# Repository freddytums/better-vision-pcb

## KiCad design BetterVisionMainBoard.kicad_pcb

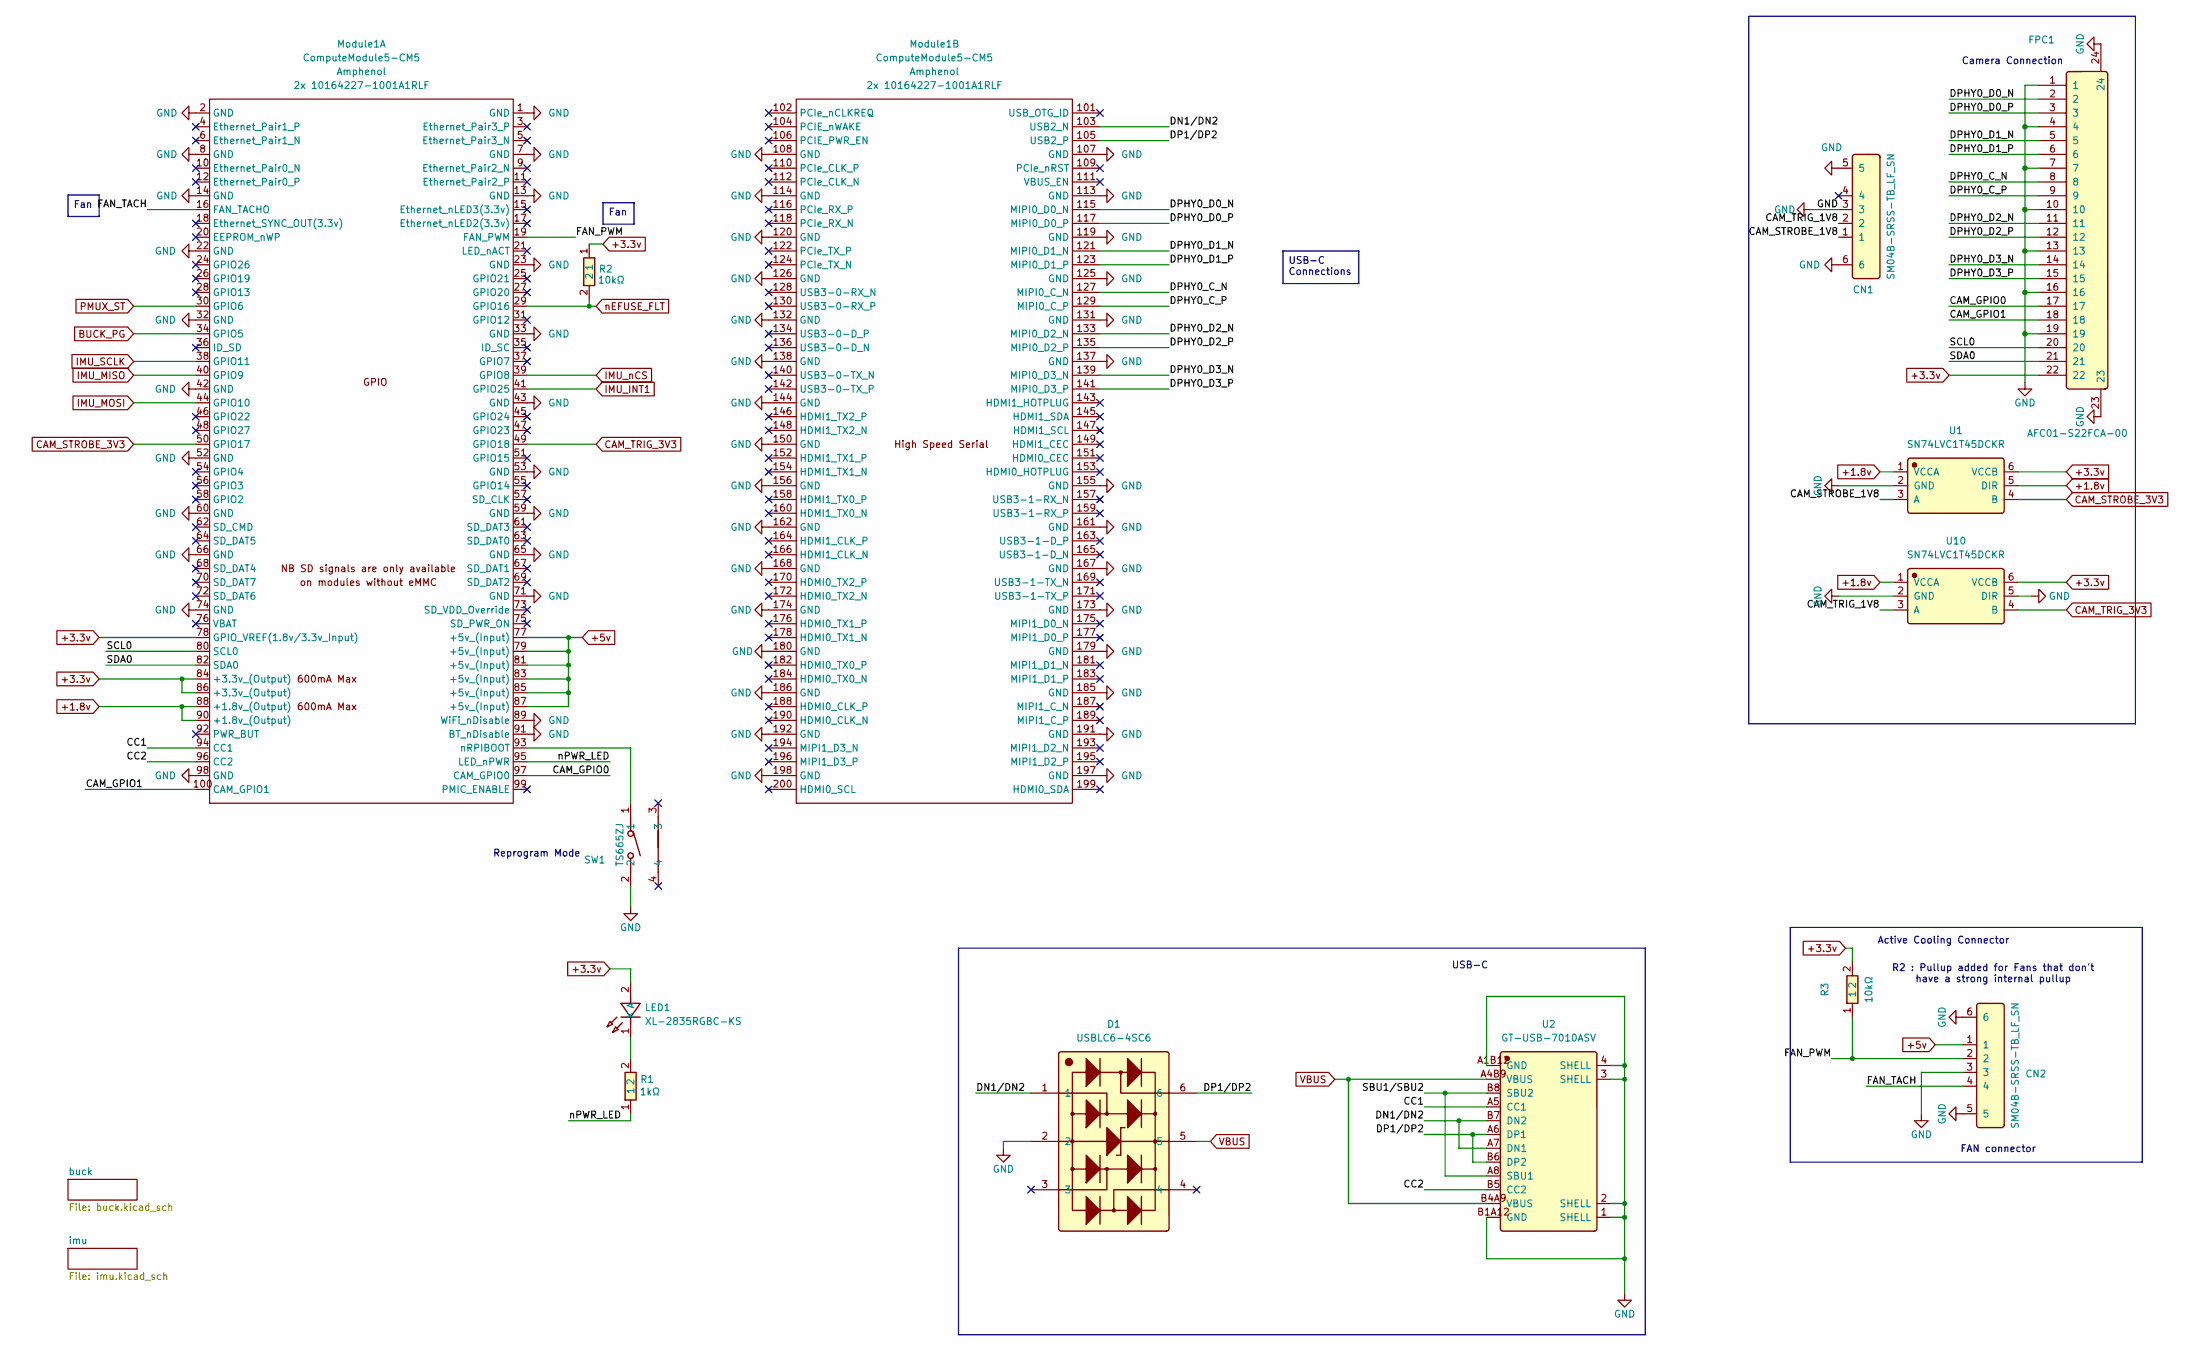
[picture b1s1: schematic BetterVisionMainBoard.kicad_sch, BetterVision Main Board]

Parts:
CN1, CN2: SM04B-SRSS-TB_LF_SN; Manufacturer Part SM04B-SRSS-TB(LF)(SN); LCSC C160404
D1: USBLC6-4SC6; MPN USBLC6-4SC6; LCSC Part C111212
FPC1: AFC01-S22FCA-00; Part Description 22 Position FFC, FPC Connector Contacts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; LCSC Part C262668
LED1: XL-2835RGBC-KS; MPN XL-2835RGBC-KS; LCSC Part C2843781
Module1: ComputeModule5-CM5; Raspberry-Pi-5-Compute-Module; MPN 10164227-1001A1RLF; LCSC Part C6782225
R1: 1kΩ; RC0402FR-071KL; Part Description Resistor 1K M1005 1% 63mW; LCSC Part C106235
R2: 10kΩ; RC0402FR-0710KL; MPN RC0402FR-0710KL; LCSC Part C60490
R3: 10kΩ; RC0402FR-0710KL; Part Description Resistor 10K M1005 1% 63mW; LCSC Part C60490
SW1: TS665ZJ; Part Description Right angle through hole Tact switch; LCSC Part C557599
U1, U10: SN74LVC1T45DCKR; MPN SN74LVC1T45DCKR; LCSC Part C9382
U2: GT-USB-7010ASV; MPN GT-USB-7010ASV; LCSC Part C2988369

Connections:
+1.8v: Module1.88 (+1.8v_(Output)), Module1.90 (+1.8v_(Output)), U1.1 (VCCA), U1.5 (DIR), U10.1 (VCCA)
+3.3v: FPC1.22, LED1.2 (A), Module1.78 (GPIO_VREF(1.8v/3.3v_Input)), Module1.84 (+3.3v_(Output)), Module1.86 (+3.3v_(Output)), R2.1, R3.2, U1.6 (VCCB), U10.6 (VCCB); also elsewhere on the board
+5v: CN2.1, Module1.77 (+5v_(Input)), Module1.79 (+5v_(Input)), Module1.81 (+5v_(Input)), Module1.83 (+5v_(Input)), Module1.85 (+5v_(Input)), Module1.87 (+5v_(Input)); also elsewhere on the board
/CAM_GPIO0: FPC1.17, Module1.97 (CAM_GPIO0)
/CAM_GPIO1: FPC1.18, Module1.100 (CAM_GPIO1)
/CAM_STROBE_1V8: CN1.1, U1.3 (A)
/CAM_TRIG_1V8: CN1.2, U10.3 (A)
/CC1: Module1.94 (CC1), U2.A5 (CC1)
/CC2: Module1.96 (CC2), U2.B5 (CC2)
/DN1/DN2: D1.1, Module1.103 (USB2_N), U2.A7 (DN1), U2.B7 (DN2)
/DP1/DP2: D1.6, Module1.105 (USB2_P), U2.A6 (DP1), U2.B6 (DP2)
/DPHY0_C_N: FPC1.8, Module1.127 (MIPI0_C_N)
/DPHY0_C_P: FPC1.9, Module1.129 (MIPI0_C_P)
/DPHY0_D0_N: FPC1.2, Module1.115 (MIPI0_D0_N)
/DPHY0_D0_P: FPC1.3, Module1.117 (MIPI0_D0_P)
/DPHY0_D1_N: FPC1.5, Module1.121 (MIPI0_D1_N)
/DPHY0_D1_P: FPC1.6, Module1.123 (MIPI0_D1_P)
/DPHY0_D2_N: FPC1.11, Module1.133 (MIPI0_D2_N)
/DPHY0_D2_P: FPC1.12, Module1.135 (MIPI0_D2_P)
/DPHY0_D3_N: FPC1.14, Module1.139 (MIPI0_D3_N)
/DPHY0_D3_P: FPC1.15, Module1.141 (MIPI0_D3_P)
/FAN_PWM: CN2.2, Module1.19 (FAN_PWM), R3.1
/FAN_TACH: CN2.4, Module1.16 (FAN_TACHO)
/SBU1/SBU2: U2.A8 (SBU1), U2.B8 (SBU2)
/SCL0: FPC1.20, Module1.80 (SCL0)
/SDA0: FPC1.21, Module1.82 (SDA0)
/nPWR_LED: Module1.95 (LED_nPWR), R1.1
BUCK_PG: Module1.34 (GPIO5); also elsewhere on the board
CAM_STROBE_3V3: Module1.50 (GPIO17), U1.4 (B)
CAM_TRIG_3V3: Module1.49 (GPIO18), U10.4 (B)
GND: CN1.3, CN1.5, CN1.6, CN2.3, CN2.5, CN2.6, D1.2, FPC1.1, FPC1.4, FPC1.7, FPC1.10, FPC1.13, FPC1.16, FPC1.19, FPC1.23, FPC1.24, Module1.1 (GND), Module1.2 (GND), Module1.7 (GND), Module1.8 (GND), Module1.13 (GND), Module1.14 (GND), Module1.22 (GND), Module1.23 (GND), Module1.32 (GND), Module1.33 (GND), Module1.42 (GND), Module1.43 (GND), Module1.52 (GND), Module1.53 (GND), Module1.59 (GND), Module1.60 (GND), Module1.65 (GND), Module1.66 (GND), Module1.71 (GND), Module1.74 (GND), Module1.89 (WiFi_nDisable), Module1.91 (BT_nDisable), Module1.98 (GND), Module1.107 (GND), Module1.108 (GND), Module1.113 (GND), Module1.114 (GND), Module1.119 (GND), Module1.120 (GND), Module1.125 (GND), Module1.126 (GND), Module1.131 (GND), Module1.132 (GND), Module1.137 (GND), Module1.138 (GND), Module1.144 (GND), Module1.150 (GND), Module1.155 (GND), Module1.156 (GND), Module1.161 (GND), Module1.162 (GND), Module1.167 (GND), Module1.168 (GND), Module1.173 (GND), Module1.174 (GND), Module1.179 (GND), Module1.180 (GND), Module1.185 (GND), Module1.186 (GND), Module1.191 (GND), Module1.192 (GND), Module1.197 (GND), Module1.198 (GND), SW1.2, U1.2 (GND), U2.1 (SHELL), U2.2 (SHELL), U2.3 (SHELL), U2.4 (SHELL), U2.A1B12 (GND), U2.B1A12 (GND), U10.2 (GND), U10.5 (DIR); also elsewhere on the board
IMU_INT1: Module1.41 (GPIO25); also elsewhere on the board
IMU_MISO: Module1.40 (GPIO9); also elsewhere on the board
IMU_MOSI: Module1.44 (GPIO10); also elsewhere on the board
IMU_SCLK: Module1.38 (GPIO11); also elsewhere on the board
IMU_nCS: Module1.39 (GPIO8); also elsewhere on the board
unnamed: LED1.1 (K), R1.2
unnamed: Module1.93 (nRPIBOOT), SW1.1
PMUX_ST: Module1.30 (GPIO6); also elsewhere on the board
VBUS: D1.5, U2.A4B9 (VBUS), U2.B4A9 (VBUS); also elsewhere on the board
nEFUSE_FLT: Module1.29 (GPIO16), R2.2; also elsewhere on the board

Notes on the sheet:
Active Cooling Connector
FAN connector
Reprogram Mode
Camera Connection
USB-C
R2 : Pullup added for Fans that don't have a strong internal pullup
Fan
USB-C Connections

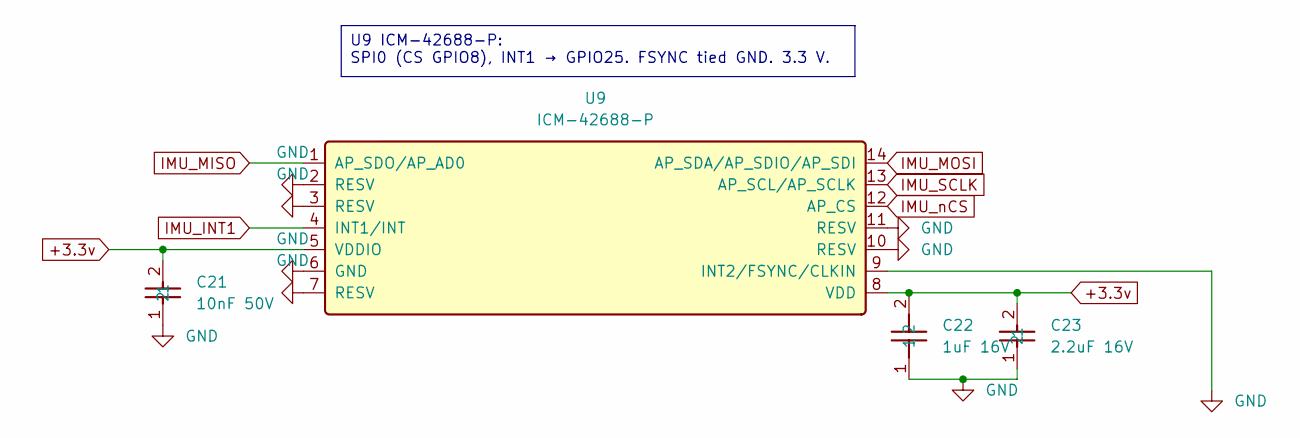
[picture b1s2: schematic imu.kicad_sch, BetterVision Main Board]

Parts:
C21: 10nF 50V; CC0402KRX7R9BB103; MPN CC0402KRX7R9BB103; LCSC Part C60133
C22: 1uF 16V; CC0402KRX5R7BB105; MPN CC0402KRX5R7BB105; LCSC Part C325464
C23: 2.2uF 16V; CL10A225KO8NNNC; MPN CL10A225KO8NNNC; LCSC Part C23630
U9: ICM-42688-P; MPN ICM-42688-P; LCSC Part C1850418

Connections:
+3.3v: C21.2, C22.2, C23.2, U9.5 (VDDIO), U9.8 (VDD); also elsewhere on the board
GND: C21.1, C22.1, C23.1, U9.2 (RESV), U9.3 (RESV), U9.6 (GND), U9.7 (RESV), U9.9 (INT2/FSYNC/CLKIN), U9.10 (RESV), U9.11 (RESV); also elsewhere on the board
IMU_INT1: U9.4 (INT1/INT); also elsewhere on the board
IMU_MISO: U9.1 (AP_SDO/AP_AD0); also elsewhere on the board
IMU_MOSI: U9.14 (AP_SDA/AP_SDIO/AP_SDI); also elsewhere on the board
IMU_SCLK: U9.13 (AP_SCL/AP_SCLK); also elsewhere on the board
IMU_nCS: U9.12 (AP_CS); also elsewhere on the board

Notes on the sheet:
U9 ICM-42688-P: SPI0 (CS GPIO8), INT1 → GPIO25. FSYNC tied GND. 3.3 V.

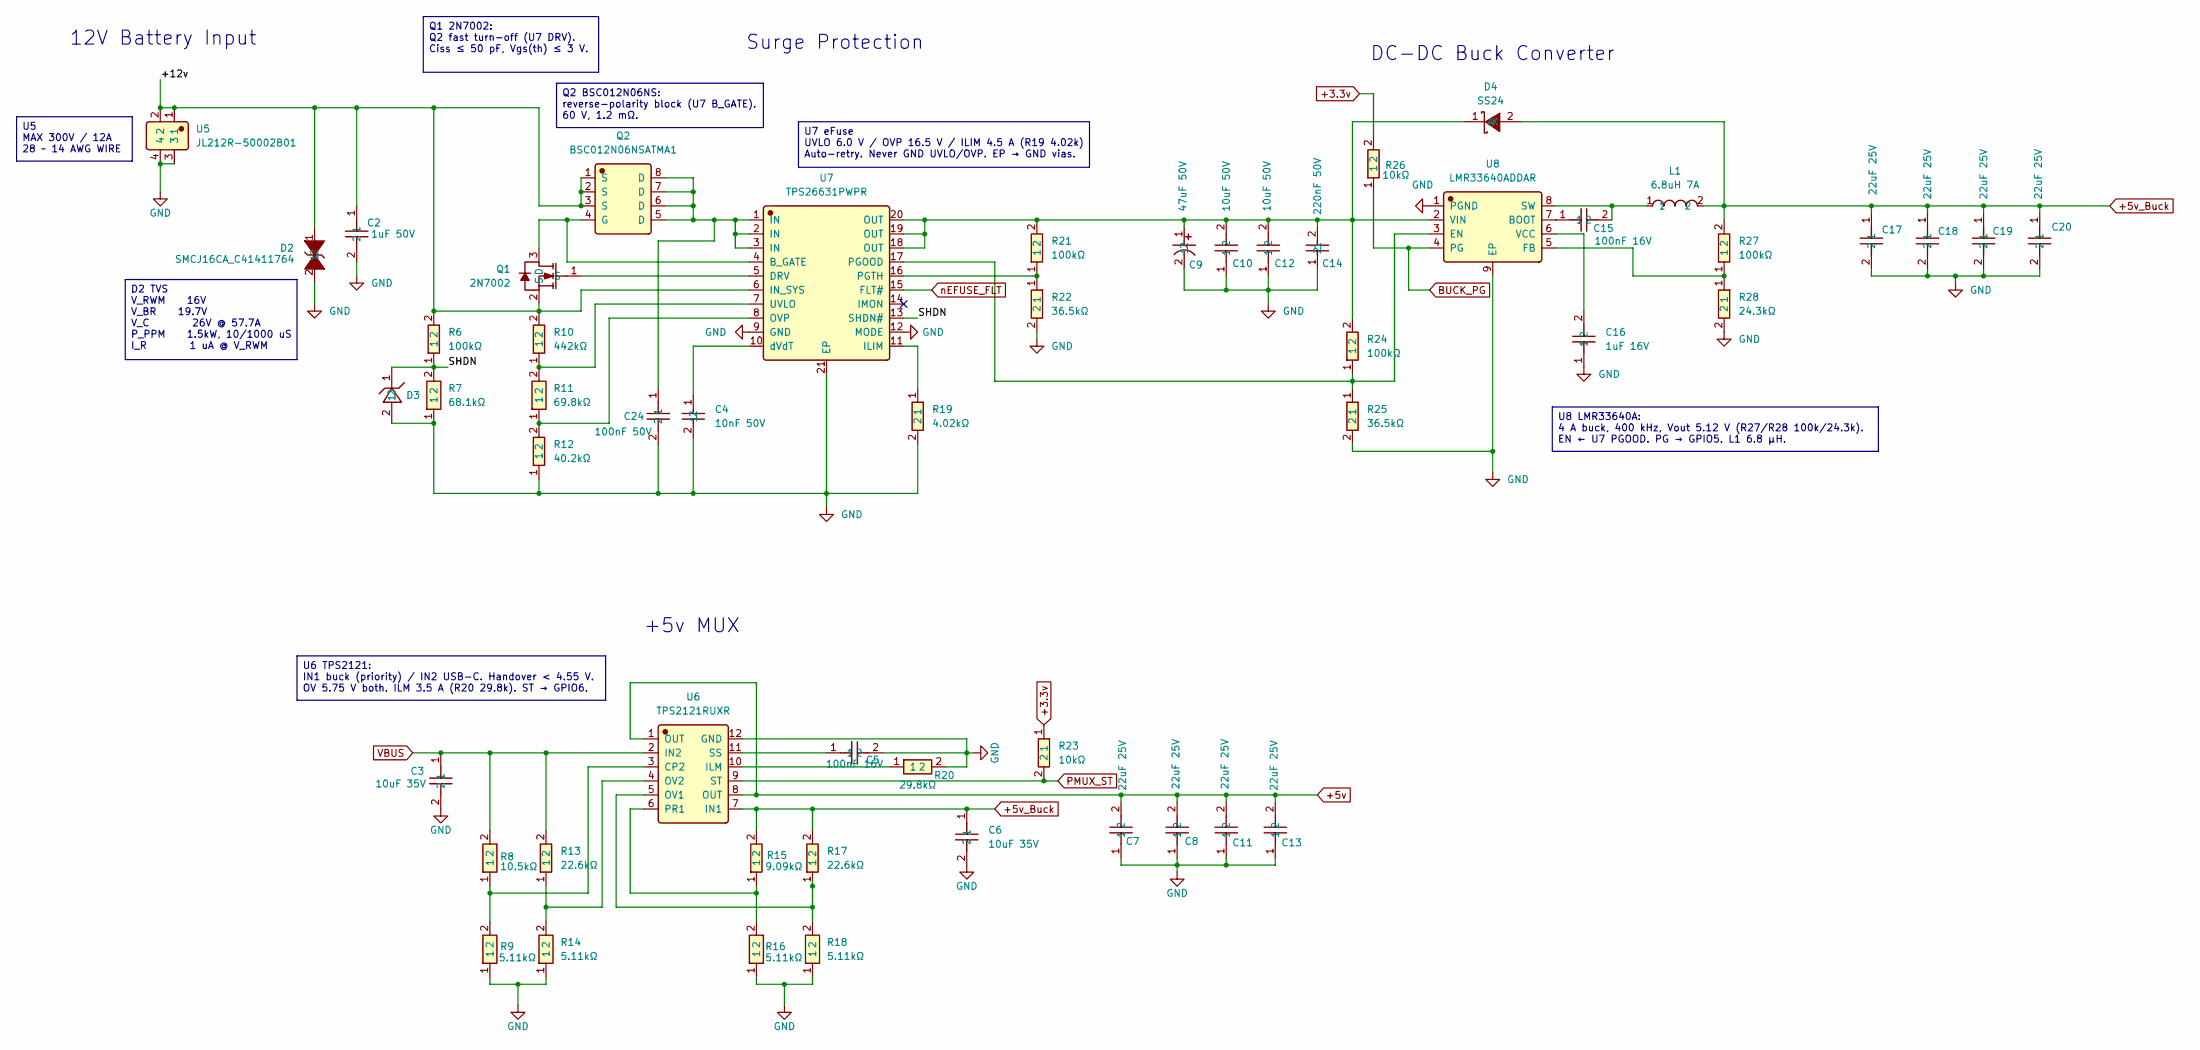
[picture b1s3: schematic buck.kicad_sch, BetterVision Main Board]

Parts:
C2: 1uF 50V; CL10A105KB8NNNC; Manufacturer Part CL10A105KB8NNNC; LCSC C15849
C3, C6: 10uF 35V; CGA0805X5R106K350MT; Manufacturer Part CGA0805X5R106K350MT; LCSC C6119888
C4: 10nF 50V; CC0402KRX7R9BB103; MPN CC0402KRX7R9BB103; LCSC Part C60133
C5, C15: 100nF 16V; CC0402KRX7R7BB104; Manufacturer Part CC0402KRX7R7BB104; LCSC C60474
C7, C8, C11, C13: 22uF 25V; CGA0805X5R226M250MT; MPN CGA0805X5R226M250MT; LCSC Part C6119899
C9: 47uF 50V; RVT1H470M0607; Manufacturer Part RVT1H470M0607; LCSC C72523
C10, C12: 10uF 50V; CL31B106KBHNNNE; Manufacturer Part CL31B106KBHNNNE; LCSC C89632
C14: 220nF 50V; CL21B224KBFNNNE; Manufacturer Part CL21B224KBFNNNE; LCSC C5378
C16: 1uF 16V; CC0402KRX5R7BB105; Manufacturer Part CC0402KRX5R7BB105; LCSC C325464
C17, C18, C19, C20: 22uF 25V; CL32A226KAJNNNE; Manufacturer Part CL32A226KAJNNNE; LCSC C52306
C24: 100nF 50V; CC0603KRX7R9BB104; Manufacturer Part CC0603KRX7R9BB104; LCSC C14663
D2: SMCJ16CA_C41411764; MPN SMCJ16CA; LCSC Part C41411764
D3: BZT52C4V7_C173408; MPN BZT52C4V7; LCSC Part C173408
D4: SS24; Manufacturer Part SS24; LCSC C50645
L1: 6.8uH 7A; ZEMS0730-6R8M; Manufacturer Part ZEMS0730-6R8M; LCSC C41415571
Q1: 2N7002; MPN 2N7002; LCSC Part C8545
Q2: BSC012N06NSATMA1; MPN BSC012N06NSATMA1; LCSC Part C6471337
R6: 100kΩ; RC0402FR-07100KL; MPN RC0402FR-07100KL; LCSC Part C60491
R7: 68.1kΩ; FRC0402F6812TS; MPN RC0402FR-0733KL; LCSC Part C138003
R8: 10.5kΩ; FRC0402F1052TS; Manufacturer Part FRC0402F1052TS; LCSC C3013149
R9, R14, R16, R18: 5.11kΩ; CRCW04025K11FKED; Manufacturer Part CRCW04025K11FKED; LCSC C2091561
R10: 442kΩ; 0402WGF4423TCE; MPN FRC0402F4023TS; LCSC Part C5126256
R11: 69.8kΩ; FRC0402F6982TS; MPN FRC0402F6042TS; LCSC Part C2998058
R12: 40.2kΩ; RC0402FR-0740K2L; MPN RC0402FR-0740K2L; LCSC Part C137983
R13, R17: 22.6kΩ; 0402WGF2262TCE; Manufacturer Part 0402WGF2262TCE; LCSC C26960
R15: 9.09kΩ; 0402WGF9091TCE; Manufacturer Part 0402WGF9091TCE; LCSC C11549
R19: 4.02kΩ; RC0402FR-074K02L; Manufacturer Part RC0402FR-074K02L; LCSC C137968
R20: 29.8kΩ; ARG03BTC2982N; Manufacturer Part ARG03BTC2982N; LCSC C2681623
R21, R24, R27: 100kΩ; RC0402FR-07100KL; Manufacturer Part RC0402FR-07100KL; LCSC C60491
R22, R25: 36.5kΩ; 0402WGF3652TCE; Manufacturer Part 0402WGF3652TCE; LCSC C25887
R23, R26: 10kΩ; RC0402FR-0710KL; Manufacturer Part RC0402FR-0710KL; LCSC C60490
R28: 24.3kΩ; 0402WGF2432TCE; Manufacturer Part 0402WGF2432TCE; LCSC C26969
U5: JL212R-50002B01; Manufacturer Part JL212R-50002B01; LCSC C2962928
U6: TPS2121RUXR; Manufacturer Part TPS2121RUXR; LCSC C485916
U7: TPS26631PWPR; MPN TPS26631PWPR; LCSC Part C2866319
U8: LMR33640ADDAR; Manufacturer Part LMR33640ADDAR; LCSC C2836966

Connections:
+3.3v: R23.1, R26.2; also elsewhere on the board
+5v: C7.2, C8.2, C11.2, C13.2, U6.1 (OUT), U6.8 (OUT); also elsewhere on the board
+5v_Buck: C6.1, C17.1, C18.1, C19.1, C20.1, D4.2 (A), L1.2, R15.2, R17.2, R27.2, U6.7 (IN1)
/buck/+12v: C2.1, D2.1, Q1.2 (S), Q2.1 (S), Q2.2 (S), Q2.3 (S), R6.2, R10.2, U5.1, U5.2, U7.6 (IN_SYS)
/buck/SHDN: D3.1, R6.1, R7.2, U7.13 (SHDN#)
BUCK_PG: R26.1, U8.4 (PG); also elsewhere on the board
GND: C2.2, C3.2, C4.2, C5.2, C6.2, C7.1, C8.1, C9.2, C10.1, C11.1, C12.1, C13.1, C14.1, C16.1, C17.2, C18.2, C19.2, C20.2, C24.2, D2.2, D3.2, R7.1, R9.1, R12.1, R14.1, R16.1, R18.1, R19.2, R20.2, R22.2, R25.2, R28.2, U5.3, U5.4, U6.12 (GND), U7.9 (GND), U7.12 (MODE), U7.21 (EP), U8.1 (PGND), U8.9 (EP); also elsewhere on the board
unnamed: C24.1, Q2.5 (D), Q2.6 (D), Q2.7 (D), Q2.8 (D), U7.1 (IN), U7.2 (IN), U7.3 (IN)
unnamed: C9.1, C10.2, C12.2, C14.2, D4.1 (K), R21.2, R24.2, U7.18 (OUT), U7.19 (OUT), U7.20 (OUT), U8.2 (VIN)
unnamed: Q1.3 (D), Q2.4 (G), U7.4 (B_GATE)
unnamed: Q1.1 (G), U7.5 (DRV)
unnamed: R8.1, R9.2, U6.3 (CP2)
unnamed: R20.1, U6.10 (ILM)
unnamed: R17.1, R18.2, U6.5 (OV1)
unnamed: R13.1, R14.2, U6.4 (OV2)
unnamed: R15.1, R16.2, U6.6 (PR1)
unnamed: C5.1, U6.11 (SS)
unnamed: R19.1, U7.11 (ILIM)
unnamed: R11.1, R12.2, U7.8 (OVP)
unnamed: R24.1, R25.1, U7.17 (PGOOD), U8.3 (EN)
unnamed: R21.1, R22.1, U7.16 (PGTH)
unnamed: R10.1, R11.2, U7.7 (UVLO)
unnamed: C4.1, U7.10 (dVdT)
unnamed: C15.1, U8.7 (BOOT)
unnamed: R27.1, R28.1, U8.5 (FB)
unnamed: C15.2, L1.1, U8.8 (SW)
unnamed: C16.2, U8.6 (VCC)
PMUX_ST: R23.2, U6.9 (ST); also elsewhere on the board
VBUS: C3.1, R8.2, R13.2, U6.2 (IN2); also elsewhere on the board
nEFUSE_FLT: U7.15 (FLT#); also elsewhere on the board

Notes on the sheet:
DC-DC Buck Converter
+5v MUX
Surge Protection
12V Battery Input
U6 TPS2121: IN1 buck (priority) / IN2 USB-C. Handover < 4.55 V. OV 5.75 V both. ILM 3.5 A (R20 29.8k). ST → GPIO6.
D2 TVS V_RWM 16V V_BR 19.7V V_C 26V @ 57.7A P_PPM 1.5kW, 10/1000 uS I_R 1 uA @ V_RWM
Q2 BSC012N06NS: reverse-polarity block (U7 B_GATE). 60 V, 1.2 mΩ.
U5 MAX 300V / 12A 28 ~ 14 AWG WIRE
U7 eFuse UVLO 6.0 V / OVP 16.5 V / ILIM 4.5 A (R19 4.02k) Auto-retry. Never GND UVLO/OVP. EP → GND vias.
U8 LMR33640A: 4 A buck, 400 kHz, Vout 5.12 V (R27/R28 100k/24.3k). EN ← U7 PGOOD. PG → GPIO5. L1 6.8 µH.
Q1 2N7002: Q2 fast turn-off (U7 DRV). Ciss ≤ 50 pF, Vgs(th) ≤ 3 V.

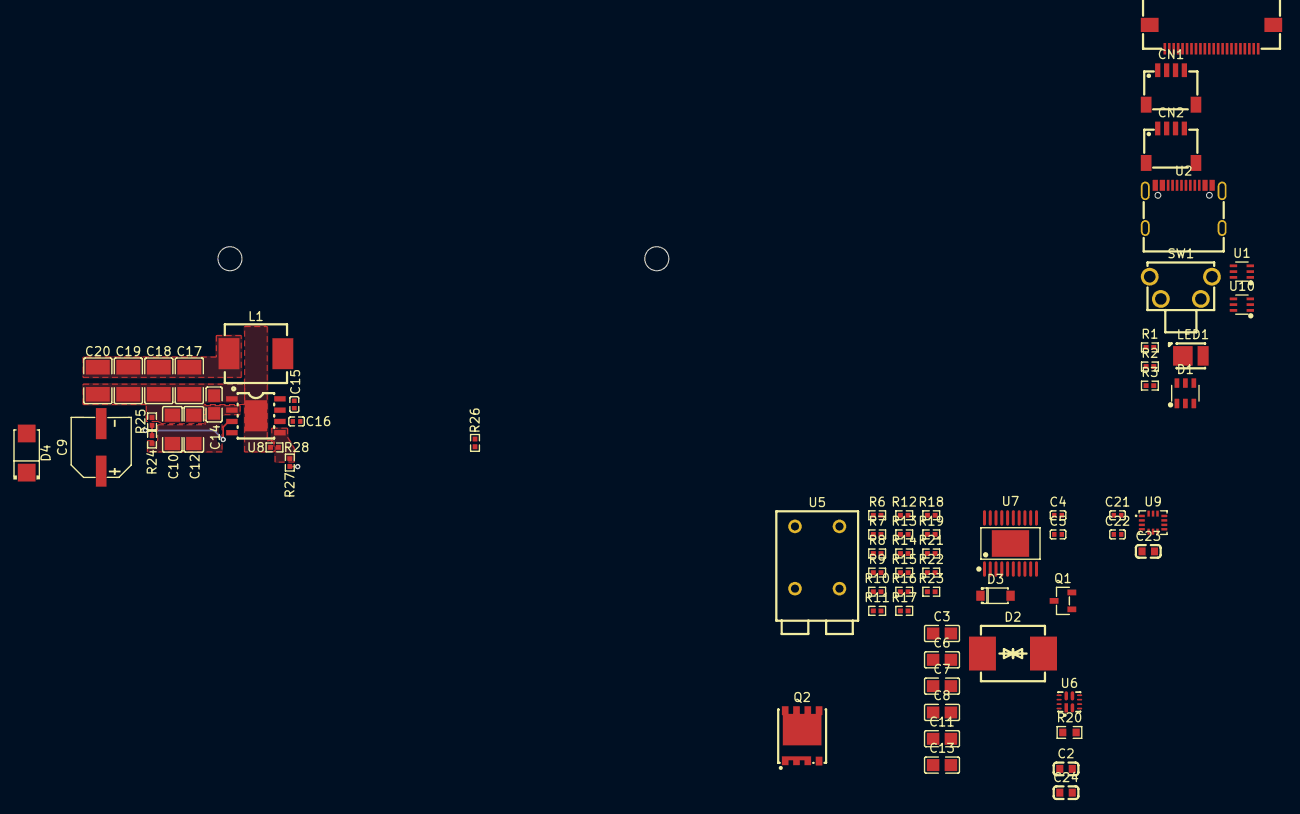
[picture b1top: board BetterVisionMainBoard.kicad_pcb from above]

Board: 2 copper layers, 70 parts (1 on the bottom side), 64 nets.

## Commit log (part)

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2026-05-31 buck-boost
2026-05-31 Added Grounds to GPIO
2026-05-31 Added Power Connector and Footprint of Buck Boost
2026-05-31 Attach Buck Footprint
2026-05-31 Progress Progress
2026-06-01 Power MUX
2026-06-01 More!
